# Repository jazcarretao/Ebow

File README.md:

# Ebow Project

PCB designs of an Electromagnetic bow (Ebow) made at Tecnun, University of Navarra, in Spain in 2012. The reference design was taken from the following video:

https://www.youtube.com/watch?v=1iccGqmEC-M

Juan Azcarreta,
Javier Bobeda

# BOM
* 1x amplifier LM386
* 1x 8-pin socket for LM386
* 1x ceramic capacitor 47nF
* 1x ceramic capacitor 1nF
* 2x electrolytic capacitor 10uF
* 1x electrolytic capacitor 220uF / 16V
* 1x resistor 10 Ohms
* 1x resistor 390 Ohm
* 1x 5mm LED (2.1V, 20mA)
* 1x 9-Volt Battery Clip
* 16 Ohms buzzer/transducer
* 1x 140 Ohms buzzer/transducer

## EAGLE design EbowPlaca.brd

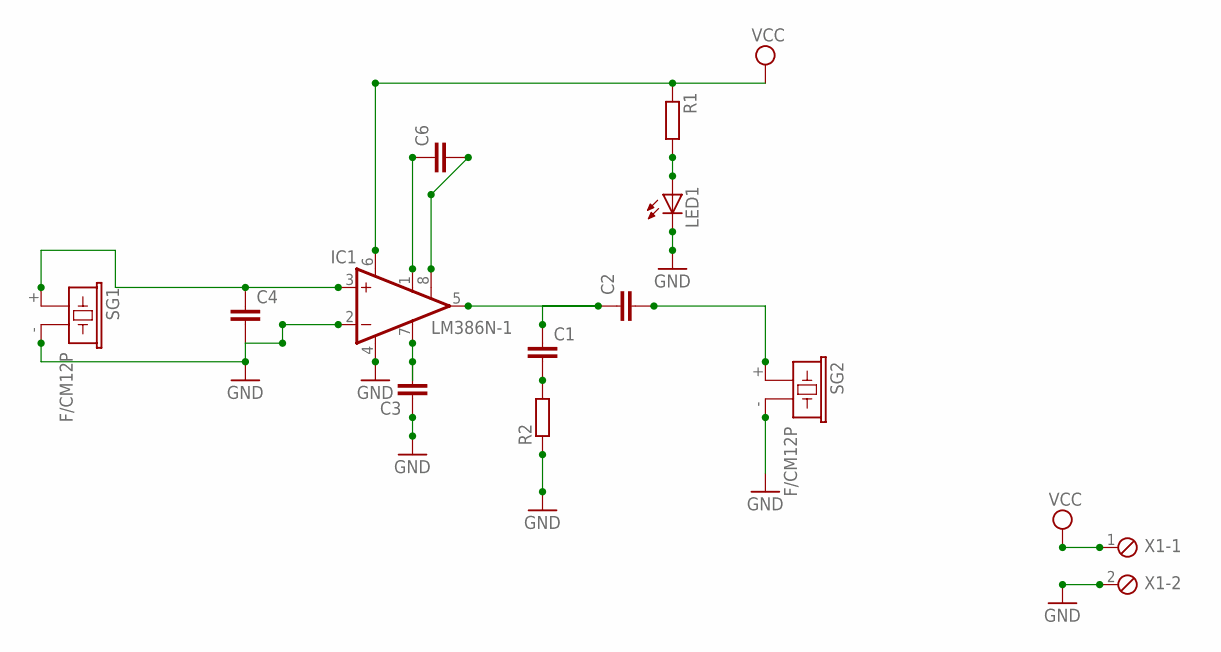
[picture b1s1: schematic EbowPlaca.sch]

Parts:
C1, C6: C5/3; C5B3
C2: C5/2.5; C5B2.5
C3: C2.5/5; C2.5-5
C4: C2.5/4; C2.5-4
IC1: LM386N-1; DIL08
LED1: LED_ELD260; LED_LD260
R1, R2: R-EU_0207/10; 0207/10
SG1, SG2: F/CM12P
X1: MPT2; 2POL254

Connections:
GND: C3.1, C4.2, IC1.2 (-IN), IC1.4 (GND), LED1.K (C), R2.1, SG1.- (2), SG2.- (2), X1.2
unnamed: C1.2, R2.2
unnamed: LED1.A, R1.2
unnamed: C6.1, IC1.1 (GAIN)
unnamed: C6.2, IC1.8 (GAIN)
unnamed: C1.1, C2.1, IC1.5 (OUT)
unnamed: C4.1, IC1.3 (+IN), SG1.+ (1)
unnamed: C3.2, IC1.7 (BYPASS)
unnamed: C2.2, SG2.+ (1)
VCC: IC1.6 (VS), R1.1, X1.1

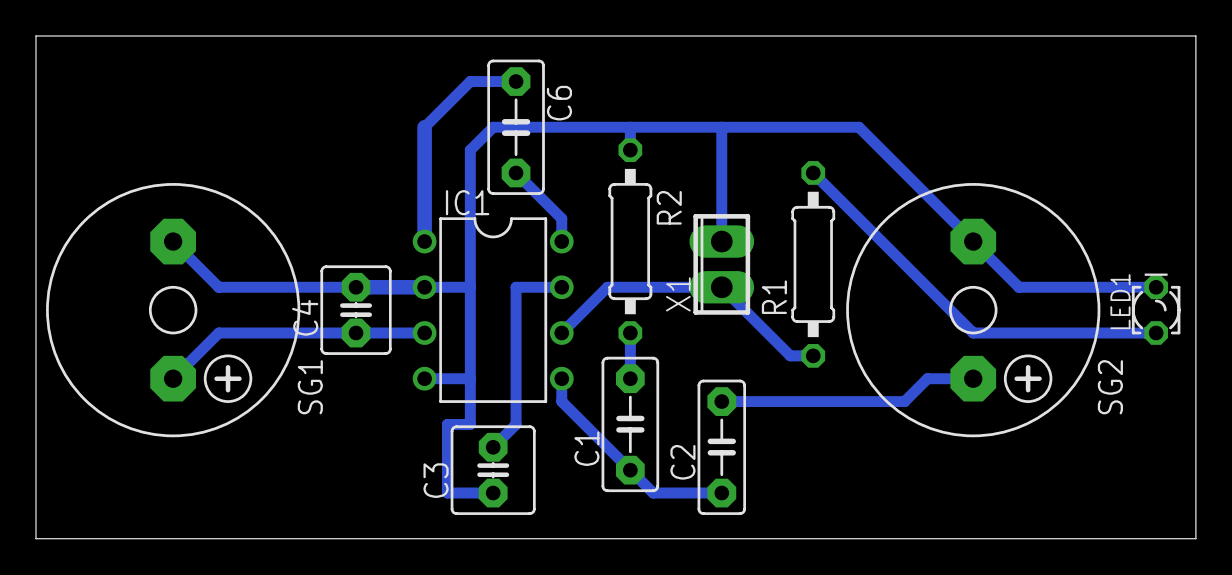
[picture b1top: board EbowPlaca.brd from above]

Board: 2 copper layers, 64.4 x 27.9 mm, 12 parts (0 on the bottom side), 10 nets.

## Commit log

2018-04-07 Created README.md
2018-10-22 Update README.md with BOM
